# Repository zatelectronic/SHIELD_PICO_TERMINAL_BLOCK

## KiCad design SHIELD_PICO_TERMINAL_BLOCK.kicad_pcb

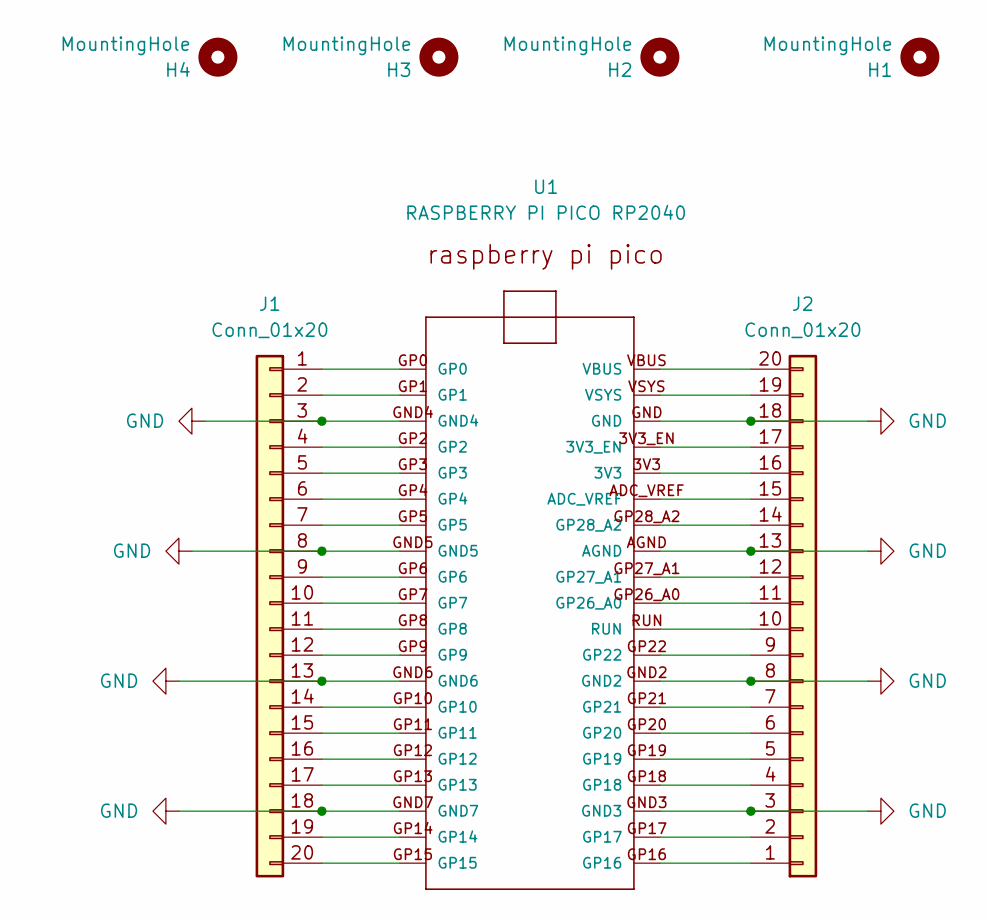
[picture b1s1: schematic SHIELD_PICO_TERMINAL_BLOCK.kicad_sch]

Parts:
H1, H2, H3, H4: MountingHole; MountingHole_3.2mm_M3_ISO14580
J1, J2: Conn_01x20; TerminalBlock_MaiXu_MX126-5.0-20P_1x20_P5.00mm
U1: RASPBERRY PI PICO RP2040; RASPBERRY_PI_PICO

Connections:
GND: J1.3, J1.8, J1.13, J1.18, J2.3, J2.8, J2.13, J2.18, U1.AGND, U1.GND, U1.GND2, U1.GND3, U1.GND4, U1.GND5, U1.GND6, U1.GND7
unnamed: J1.1, U1.GP0
unnamed: J1.2, U1.GP1
unnamed: J1.4, U1.GP2
unnamed: J1.5, U1.GP3
unnamed: J1.6, U1.GP4
unnamed: J1.7, U1.GP5
unnamed: J1.9, U1.GP6
unnamed: J1.10, U1.GP7
unnamed: J1.11, U1.GP8
unnamed: J1.12, U1.GP9
unnamed: J1.14, U1.GP10
unnamed: J1.15, U1.GP11
unnamed: J1.16, U1.GP12
unnamed: J1.17, U1.GP13
unnamed: J1.19, U1.GP14
unnamed: J1.20, U1.GP15
unnamed: J2.1, U1.GP16
unnamed: J2.2, U1.GP17
unnamed: J2.4, U1.GP18
unnamed: J2.5, U1.GP19
unnamed: J2.6, U1.GP20
unnamed: J2.7, U1.GP21
unnamed: J2.9, U1.GP22
unnamed: J2.10, U1.RUN
unnamed: J2.11, U1.GP26_A0
unnamed: J2.12, U1.GP27_A1
unnamed: J2.14, U1.GP28_A2
unnamed: J2.15, U1.ADC_VREF
unnamed: J2.16, U1.3V3
unnamed: J2.17, U1.3V3_EN
unnamed: J2.19, U1.VSYS
unnamed: J2.20, U1.VBUS

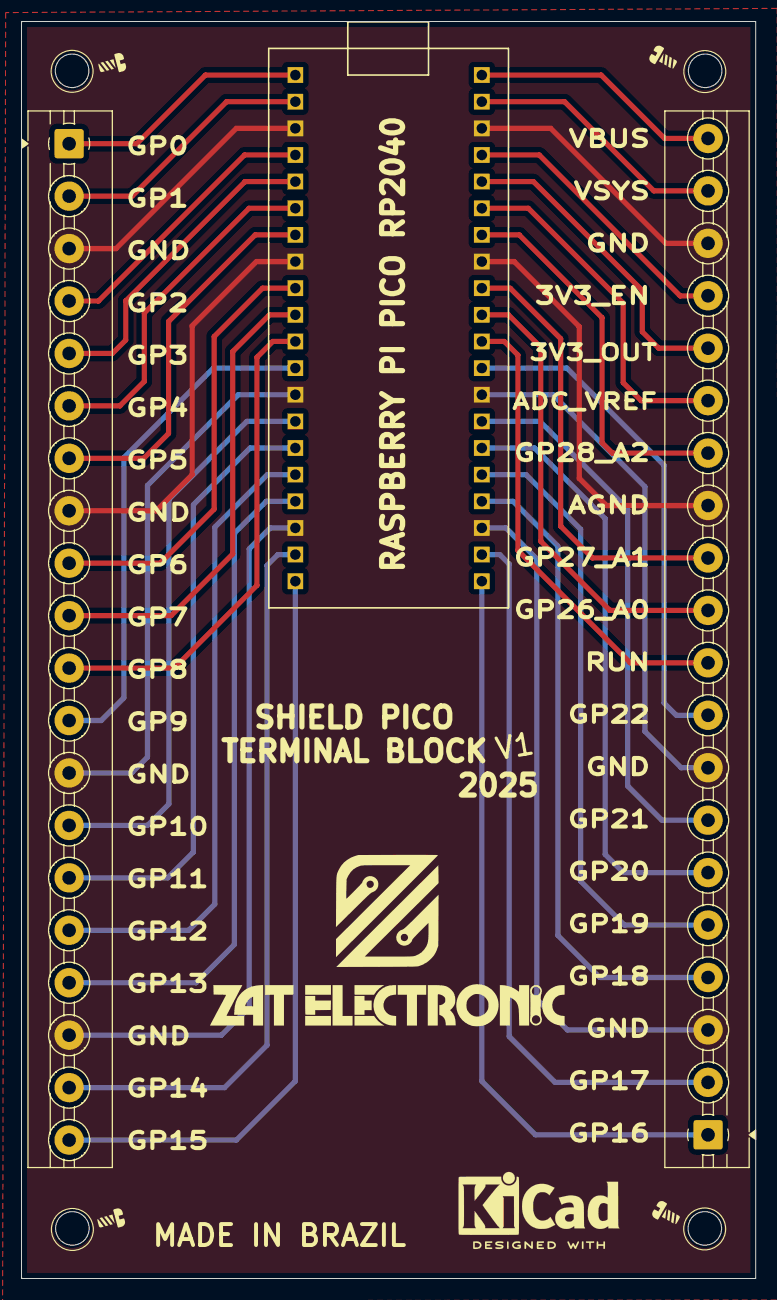
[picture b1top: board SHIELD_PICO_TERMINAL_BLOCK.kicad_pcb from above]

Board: 2 copper layers, 70.0 x 119.8 mm, 7 parts (0 on the bottom side), 33 nets.

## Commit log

2026-06-03 COMMIT-02-06-26
